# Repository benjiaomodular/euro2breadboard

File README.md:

# euro2breadboard

A simple breadboard power adapter for Eurorack module development.

## Versions
### v1.1 Quick fixes
- Spacing of power rail pins was fixed.
- Updated footprint of toggle switch. Made the drill holes a bit wider.
- Switched the position of the toggle and the LEDs so you can see the lights better.

### v1.0 Initial design
- Power rails work great.
- Holes of toggle switch were a bit too tight.
- Spacing of outer pins off with actual breadboard power rails. Can be resolved by soldering while installed on breadboard.

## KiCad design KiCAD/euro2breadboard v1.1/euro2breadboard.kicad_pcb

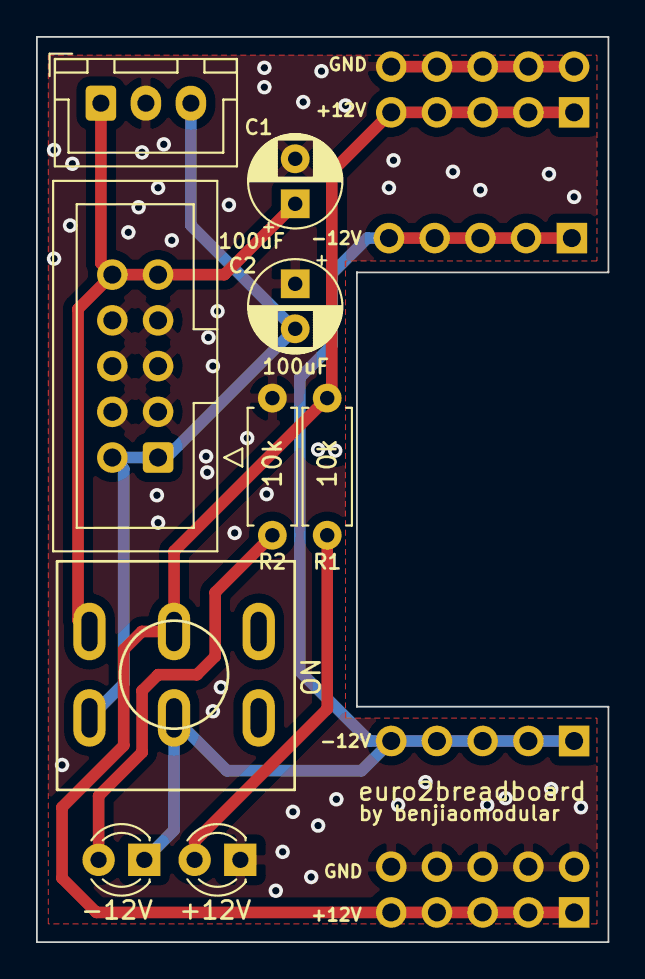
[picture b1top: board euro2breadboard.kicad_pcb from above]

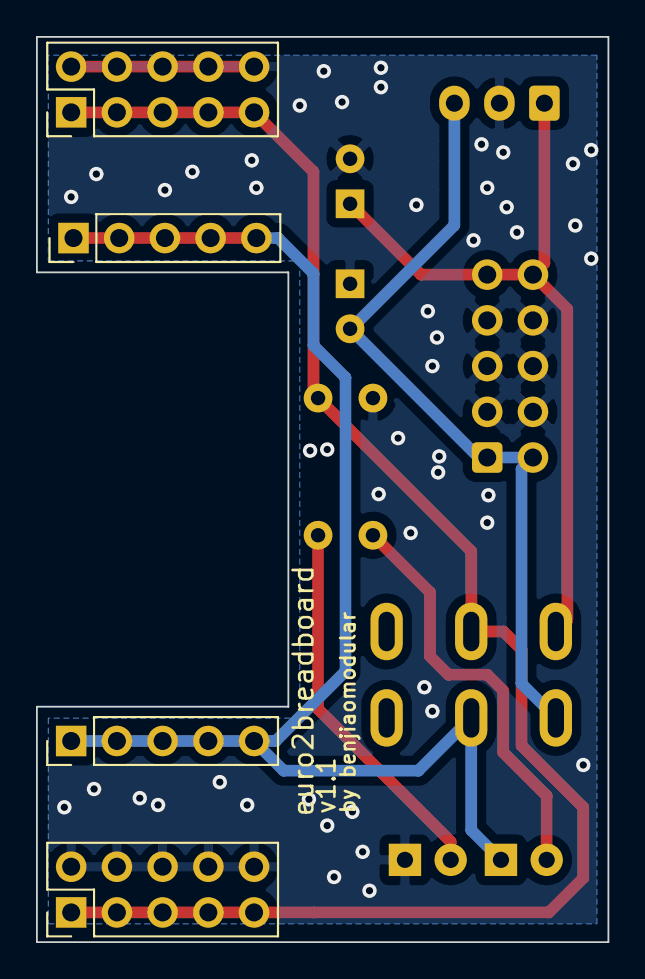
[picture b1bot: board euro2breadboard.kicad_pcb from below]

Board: 2 copper layers, 31.8 x 50.3 mm, 13 parts (4 on the bottom side), 7 nets.

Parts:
+12V: LED; LED_D3.0mm
-12V: LED; LED_D3.0mm
BB_POWER_PINS1, BB_POWER_PINS2: Conn_02x05_Odd_Even; PinHeader_2x05_P2.54mm_Vertical
C1, C2: 100uF; CP_Radial_D5.0mm_P2.50mm
J1: JST_BUS; JST_XH_B3B-XH-A_1x03_P2.50mm_Vertical
J2: IDC_BUS; IDC-Header_2x05_P2.54mm_Vertical
NEG_12V_PINS1, NEG_12V_PINS2: Conn_01x05_Male; PinHeader_1x05_P2.54mm_Vertical
R1, R2: 10k; Resistor_L6.3mm_D2.5mm_P7.62mm_Horizontal
SW1: SW_DPDT_x2; ToggleSwitch_MTS-202_DPDT

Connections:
+12V: C1.1, J1.1, J2.9, J2.10, SW1.3
-12V: C2.2, J1.3, J2.1, J2.2, SW1.6
GND: +12V.1, BB_POWER_PINS1.2, BB_POWER_PINS1.4, BB_POWER_PINS1.6, BB_POWER_PINS1.8, BB_POWER_PINS1.10, BB_POWER_PINS2.2, BB_POWER_PINS2.4, BB_POWER_PINS2.6, BB_POWER_PINS2.8, BB_POWER_PINS2.10, C1.2, C2.1, J1.2, J2.3, J2.4, J2.5, J2.6, J2.7, J2.8, R2.2
unnamed: BB_POWER_PINS1.1, BB_POWER_PINS1.3, BB_POWER_PINS1.5, BB_POWER_PINS1.7, BB_POWER_PINS1.9, BB_POWER_PINS2.1, BB_POWER_PINS2.3, BB_POWER_PINS2.5, BB_POWER_PINS2.7, BB_POWER_PINS2.9, R1.2, SW1.2
unnamed: -12V.1, NEG_12V_PINS1.1, NEG_12V_PINS1.2, NEG_12V_PINS1.3, NEG_12V_PINS1.4, NEG_12V_PINS1.5, NEG_12V_PINS2.1, NEG_12V_PINS2.2, NEG_12V_PINS2.3, NEG_12V_PINS2.4, NEG_12V_PINS2.5, SW1.5
unnamed: -12V.2, R2.1
unnamed: +12V.2, R1.1

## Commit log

2022-02-06 Added license file
2022-02-06 Updated license date
2022-02-06 Added initial readme contents
2022-02-06 Fixed board dimensions
2022-02-19 Added v1.1 layout
2022-02-19 Updated docs
2022-02-19 Added gerber files
2022-04-02 more layout tweaks
2022-05-10 Added svg export
